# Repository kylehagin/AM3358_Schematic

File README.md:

# AM3358_Schematic
AM3358 Schematic with ram, lcds, and sd card interface.

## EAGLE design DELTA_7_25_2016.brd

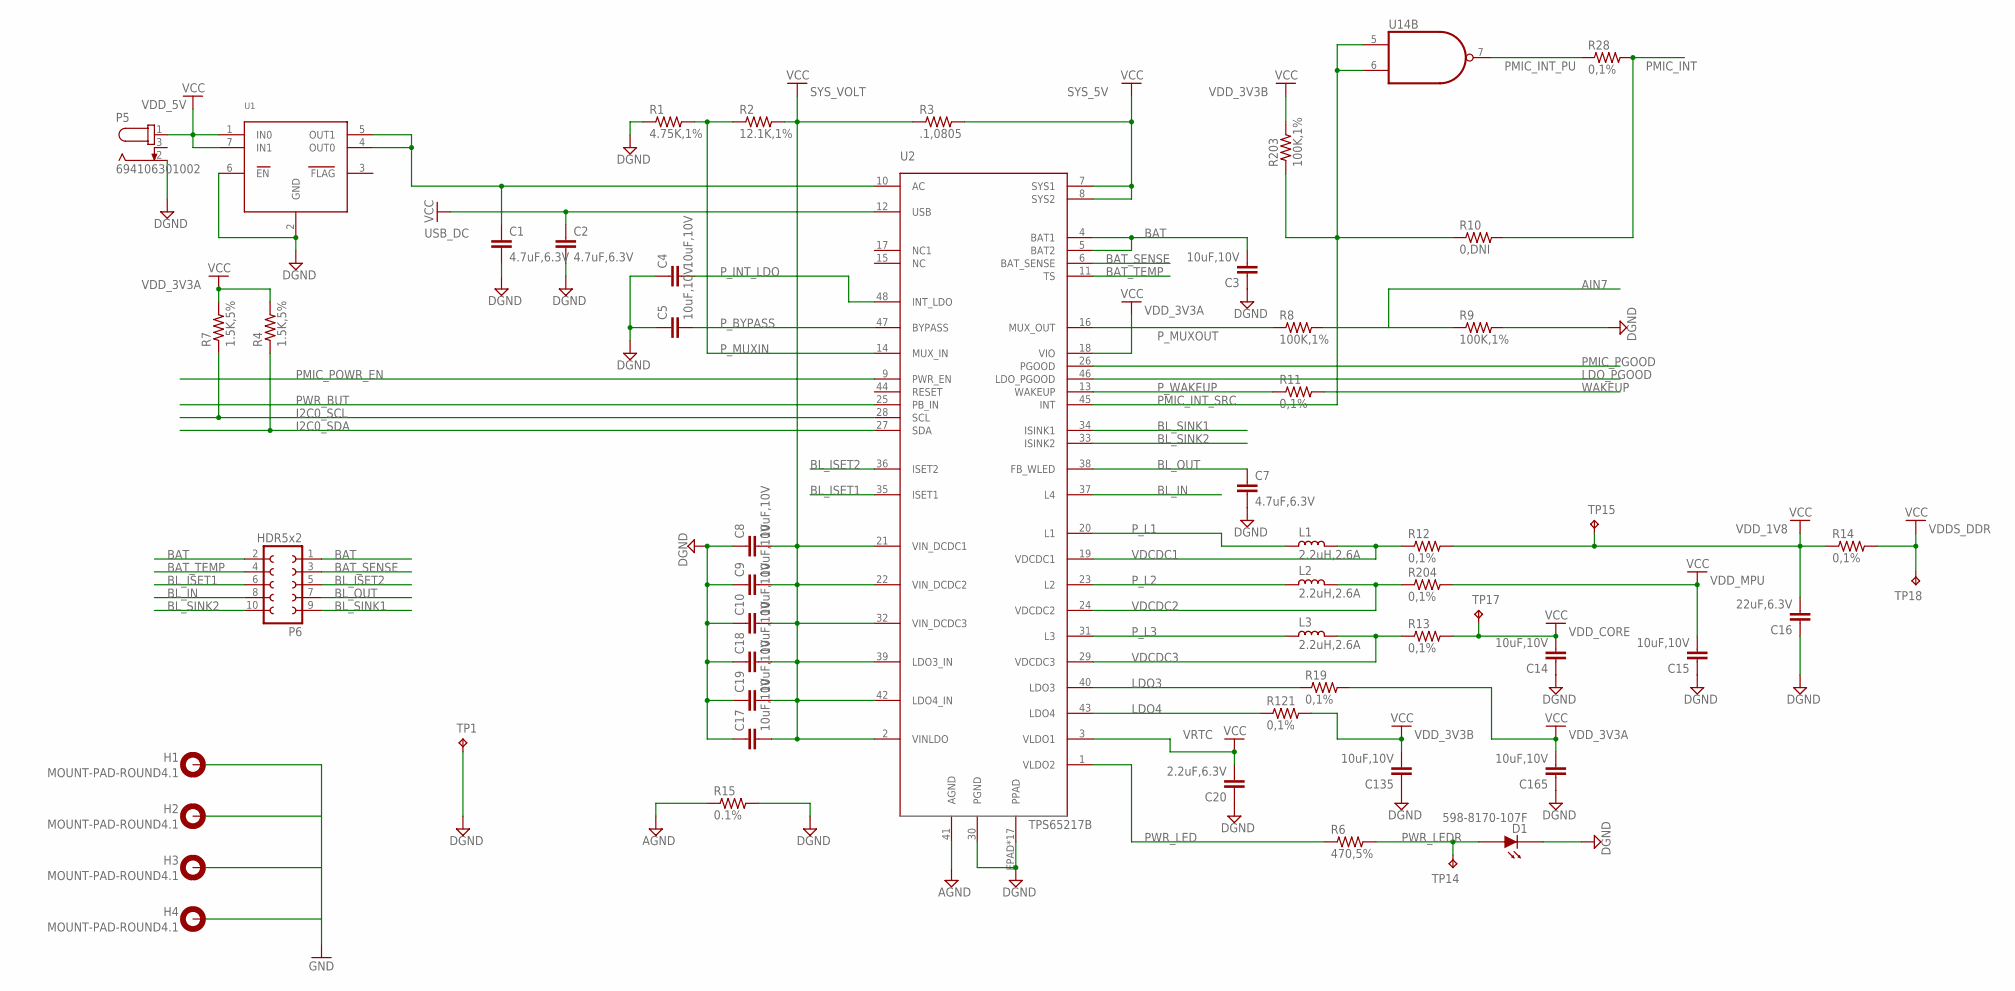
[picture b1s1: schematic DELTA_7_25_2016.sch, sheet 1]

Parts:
C1, C2, C7: 4.7uF,6.3V; C0402
C3, C4, C5, C8, C9, C10, C14, C15, C17, C18, C19, C135, C165: 10uF,10V; C0402
C16: 22uF,6.3V; C0402
C20: 2.2uF,6.3V; C0402
D1: 598-8170-107F; 0805P
H1, H2, H3, H4: MOUNT-PAD-ROUND4.1; 4,1-PAD
L1, L2, L3: 2.2uH,2.6A; L1008
P5: 694106301002
P6: HDR5x2; FE05-2
R1: 4.75K,1%; R0402
R2: 12.1K,1%; R0402
R3: .1,0805; R0402
R4, R7: 1.5K,5%; R0402
R6: 470,5%; R0402
R8, R9, R203: 100K,1%; R0402
R10: 0,DNI; R0402
R11, R12, R13, R14, R19, R28, R121, R204: 0,1%; R0402
R15: 0.1%; R0402
TP1, TP14, TP15, TP17, TP18: TPB1,27; B1,27
U1: NCP349; DFN6
U2: TPS65217B; RSL(S-PVQFN-N48)
U14: SN74LVC2G00DCU; DCU(S-PDSO-G8)

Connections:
AGND: R15.1, U2.41 (AGND)
AIN7: R8.2, R9.1; also elsewhere on the board
BAT: C3.2, P6.1, P6.2, U2.4 (BAT1), U2.5 (BAT2)
BAT_SENSE: P6.3, U2.6 (BAT_SENSE)
BAT_TEMP: P6.4, U2.11 (TS)
BL_IN: P6.8, U2.37 (L4)
BL_ISET1: P6.6, U2.35 (ISET1)
BL_ISET2: P6.5, U2.36 (ISET2)
BL_OUT: C7.1, P6.7, U2.38 (FB_WLED)
BL_SINK1: P6.9, U2.34 (ISINK1)
BL_SINK2: P6.10, U2.33 (ISINK2)
DGND: C1.2, C2.2, C3.1, C4.1, C5.1, C7.2, C8.1, C9.1, C10.1, C14.1, C15.1, C16.1, C17.1, C18.1, C19.1, C20.1, C135.1, C165.1, D1.2 (D_OUT), P5.2, R1.1, R9.2, R15.2, TP1.TP, U1.2 (GND), U1.6 (EN), U2.30 (PGND), U2.EPAD (PPAD), U2.P$1 (PPAD), U2.P$2 (PPAD), U2.P$3 (PPAD), U2.P$4 (PPAD), U2.P$5 (PPAD), U2.P$6 (PPAD), U2.P$7 (PPAD), U2.P$8 (PPAD), U2.P$9 (PPAD), U2.P$10 (PPAD), U2.P$11 (PPAD), U2.P$12 (PPAD), U2.P$13 (PPAD), U2.P$14 (PPAD), U2.P$15 (PPAD), U2.P$16 (PPAD); also elsewhere on the board
GND: H1.B4,1, H2.B4,1, H3.B4,1, H4.B4,1; also elsewhere on the board
I2C0_SCL: R7.1, U2.28 (SCL); also elsewhere on the board
I2C0_SDA: R4.1, U2.27 (SDA); also elsewhere on the board
LDO3: R19.1, U2.40 (LDO3)
LDO4: R121.1, U2.43 (LDO4)
LDO_PGOOD: U2.46 (LDO_PGOOD); also elsewhere on the board
unnamed: C1.1, U1.4 (OUT0), U1.5 (OUT1), U2.10 (AC)
PMIC_INT: R10.2, R28.2; also elsewhere on the board
PMIC_INT_PU: R28.1, U14.7 (O)
PMIC_INT_SRC: R10.1, R203.1, U2.45 (INT), U14.5 (I0), U14.6 (I1)
PMIC_PGOOD: U2.26 (PGOOD); also elsewhere on the board
PMIC_POWR_EN: U2.9 (PWR_EN); also elsewhere on the board
PWR_BUT: U2.25 (PB_IN); also elsewhere on the board
PWR_LED: R6.1, U2.1 (VLDO2)
PWR_LEDR: D1.1 (D_IN), R6.2, TP14.TP
P_BYPASS: C5.2, U2.47 (BYPASS)
P_INT_LDO: C4.2, U2.48 (INT_LDO)
P_L1: L1.2, U2.20 (L1)
P_L2: L2.2, U2.23 (L2)
P_L3: L3.2, U2.31 (L3)
P_MUXIN: R1.2, R2.1, U2.14 (MUX_IN)
P_MUXOUT: R8.1, U2.16 (MUX_OUT)
P_WAKEUP: R11.1, U2.13 (WAKEUP)
SYS_5V: R3.2, U2.7 (SYS1), U2.8 (SYS2); also elsewhere on the board
SYS_VOLT: C8.2, C9.2, C10.2, C17.2, C18.2, C19.2, R2.2, R3.1, U2.2 (VINLDO), U2.21 (VIN_DCDC1), U2.22 (VIN_DCDC2), U2.32 (VIN_DCDC3), U2.39 (LDO3_IN), U2.42 (LDO4_IN); also elsewhere on the board
USB_DC: C2.1, U2.12 (USB); also elsewhere on the board
VDCDC1: L1.1, R12.1, U2.19 (VDCDC1)
VDCDC2: L2.1, R204.1, U2.24 (VDCDC2)
VDCDC3: L3.1, R13.1, U2.29 (VDCDC3)
VDDS_DDR: R14.2, TP18.TP; also elsewhere on the board
VDD_1V8: C16.2, R12.2, R14.1, TP15.TP; also elsewhere on the board
VDD_3V3A: C165.2, R4.2, R7.2, R19.2, U2.18 (VIO); also elsewhere on the board
VDD_3V3B: C135.2, R121.2, R203.2; also elsewhere on the board
VDD_5V: P5.1, U1.1 (IN0), U1.7 (IN1); also elsewhere on the board
VDD_CORE: C14.2, R13.2, TP17.TP; also elsewhere on the board
VDD_MPU: C15.2, R204.2; also elsewhere on the board
VRTC: C20.2, U2.3 (VLDO1); also elsewhere on the board
WAKEUP: R11.2; also elsewhere on the board

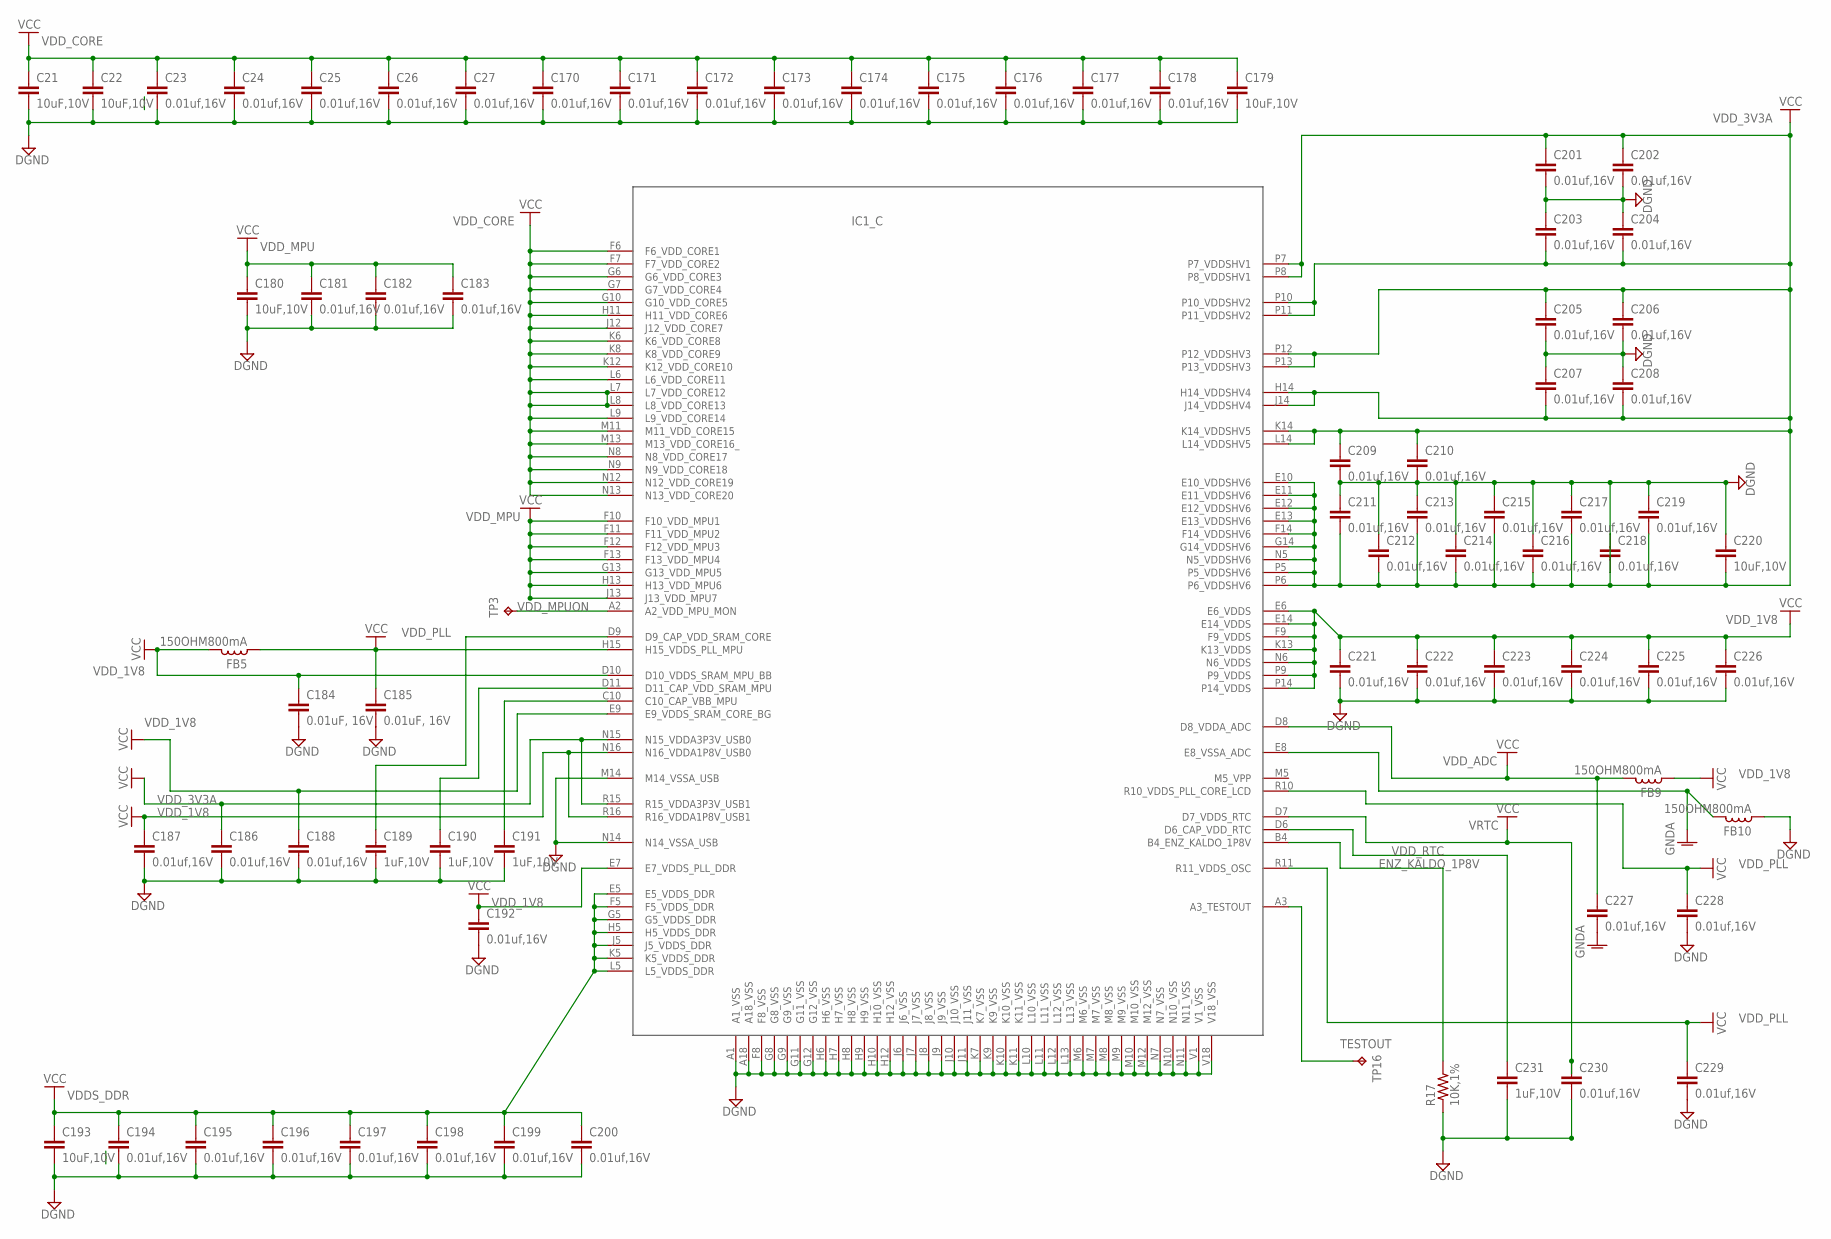
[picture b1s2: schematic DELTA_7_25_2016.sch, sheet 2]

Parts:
C21, C22, C179, C180, C193, C220: 10uF,10V; C0402
C23, C24, C25, C26, C27, C170, C171, C172, C173, C174, C175, C176, C177, C178, C181, C182, C183, C186, C187, C188, C192, C194, C195, C196, C197, C198, C199, C200, C201, C202, C203, C204, C205, C206, C207, C208, C209, C210, C211, C212, C213, C214, C215, C216, C217, C218, C219, C221, C222, C223, C224, C225, C226, C227, C228, C229, C230: 0.01uf,16V; C0402
C184, C185: 0.01uF, 16V; C0402
C189, C190, C191, C231: 1uF,10V; C0402
FB5, FB9: 150OHM800mA; L0603
FB10: 150OHM800mA; L1812
IC1: AM335X_ZCZ; ZCZ_S-PBGA-N324
R17: 10K,1%; R0402
TP3, TP16: TPB1,27; B1,27

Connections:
DGND: C21.2, C22.2, C23.2, C24.2, C25.2, C26.2, C27.2, C170.2, C171.2, C172.2, C173.2, C174.2, C175.2, C176.2, C177.2, C178.2, C179.2, C180.2, C181.2, C182.2, C183.2, C184.2, C185.2, C186.2, C187.2, C188.2, C189.2, C190.2, C191.2, C192.2, C193.2, C194.2, C195.2, C196.2, C197.2, C198.2, C199.2, C200.2, C201.2, C202.2, C203.1, C204.1, C205.2, C206.2, C207.1, C208.1, C221.2, C222.2, C223.2, C224.2, C225.2, C226.2, C228.2, C229.2, C230.2, C231.2, FB10.2, IC1.A1 (A1_VSS), IC1.A18 (A18_VSS), IC1.F8 (F8_VSS), IC1.G8 (G8_VSS), IC1.G9 (G9_VSS), IC1.G11 (G11_VSS), IC1.G12 (G12_VSS), IC1.H6 (H6_VSS), IC1.H7 (H7_VSS), IC1.H8 (H8_VSS), IC1.H9 (H9_VSS), IC1.H10 (H10_VSS), IC1.H12 (H12_VSS), IC1.J6 (J6_VSS), IC1.J7 (J7_VSS), IC1.J8 (J8_VSS), IC1.J9 (J9_VSS), IC1.J10 (J10_VSS), IC1.J11 (J11_VSS), IC1.K7 (K7_VSS), IC1.K9 (K9_VSS), IC1.K10 (K10_VSS), IC1.K11 (K11_VSS), IC1.L10 (L10_VSS), IC1.L11 (L11_VSS), IC1.L12 (L12_VSS), IC1.L13 (L13_VSS), IC1.M6 (M6_VSS), IC1.M7 (M7_VSS), IC1.M8 (M8_VSS), IC1.M9 (M9_VSS), IC1.M10 (M10_VSS), IC1.M12 (M12_VSS), IC1.M14 (M14_VSSA_USB), IC1.N7 (N7_VSS), IC1.N10 (N10_VSS), IC1.N11 (N11_VSS), IC1.N14 (N14_VSSA_USB), IC1.V1 (V1_VSS), IC1.V18 (V18_VSS), R17.1; also elsewhere on the board
ENZ_KALDO_1P8V: IC1.B4 (B4_ENZ_KALDO_1P8V), R17.2
GNDA: C227.2, FB10.1, IC1.E8 (E8_VSSA_ADC); also elsewhere on the board
unnamed: C189.1, IC1.D9 (D9_CAP_VDD_SRAM_CORE)
unnamed: C190.1, IC1.D11 (D11_CAP_VDD_SRAM_MPU)
unnamed: C191.1, IC1.C10 (C10_CAP_VBB_MPU)
TESTOUT: IC1.A3 (A3_TESTOUT), TP16.TP
VDDS_DDR: C193.1, C194.1, C195.1, C196.1, C197.1, C198.1, C199.1, C200.1, IC1.E5 (E5_VDDS_DDR), IC1.F5 (F5_VDDS_DDR), IC1.G5 (G5_VDDS_DDR), IC1.H5 (H5_VDDS_DDR), IC1.J5 (J5_VDDS_DDR), IC1.K5 (K5_VDDS_DDR), IC1.L5 (L5_VDDS_DDR); also elsewhere on the board
VDD_1V8: C184.1, C187.1, C188.1, C192.1, C221.1, C222.1, C223.1, C224.1, C225.1, C226.1, FB5.1, FB9.2, IC1.D10 (D10_VDDS_SRAM_MPU_BB), IC1.E6 (E6_VDDS), IC1.E7 (E7_VDDS_PLL_DDR), IC1.E9 (E9_VDDS_SRAM_CORE_BG), IC1.E14 (E14_VDDS), IC1.F9 (F9_VDDS), IC1.K13 (K13_VDDS), IC1.N6 (N6_VDDS), IC1.N16 (N16_VDDA1P8V_USB0), IC1.P9 (P9_VDDS), IC1.P14 (P14_VDDS), IC1.R16 (R16_VDDA1P8V_USB1); also elsewhere on the board
VDD_3V3A: C186.1, C201.1, C202.1, C203.2, C204.2, C205.1, C206.1, C207.2, C208.2, C209.1, C209.2, C210.1, C210.2, C211.1, C211.2, C212.1, C212.2, C213.1, C213.2, C214.1, C214.2, C215.1, C215.2, C216.1, C216.2, C217.1, C217.2, C218.1, C218.2, C219.1, C219.2, C220.1, C220.2, IC1.E10 (E10_VDDSHV6), IC1.E11 (E11_VDDSHV6), IC1.E12 (E12_VDDSHV6), IC1.E13 (E13_VDDSHV6), IC1.F14 (F14_VDDSHV6), IC1.G14 (G14_VDDSHV6), IC1.H14 (H14_VDDSHV4), IC1.J14 (J14_VDDSHV4), IC1.K14 (K14_VDDSHV5), IC1.L14 (L14_VDDSHV5), IC1.N5 (N5_VDDSHV6), IC1.N15 (N15_VDDA3P3V_USB0), IC1.P5 (P5_VDDSHV6), IC1.P6 (P6_VDDSHV6), IC1.P7 (P7_VDDSHV1), IC1.P8 (P8_VDDSHV1), IC1.P10 (P10_VDDSHV2), IC1.P11 (P11_VDDSHV2), IC1.P12 (P12_VDDSHV3), IC1.P13 (P13_VDDSHV3), IC1.R15 (R15_VDDA3P3V_USB1); also elsewhere on the board
VDD_ADC: C227.1, FB9.1, IC1.D8 (D8_VDDA_ADC); also elsewhere on the board
VDD_CORE: C21.1, C22.1, C23.1, C24.1, C25.1, C26.1, C27.1, C170.1, C171.1, C172.1, C173.1, C174.1, C175.1, C176.1, C177.1, C178.1, C179.1, IC1.F6 (F6_VDD_CORE1), IC1.F7 (F7_VDD_CORE2), IC1.G6 (G6_VDD_CORE3), IC1.G7 (G7_VDD_CORE4), IC1.G10 (G10_VDD_CORE5), IC1.H11 (H11_VDD_CORE6), IC1.J12 (J12_VDD_CORE7), IC1.K6 (K6_VDD_CORE8), IC1.K8 (K8_VDD_CORE9), IC1.K12 (K12_VDD_CORE10), IC1.L6 (L6_VDD_CORE11), IC1.L7 (L7_VDD_CORE12), IC1.L8 (L8_VDD_CORE13), IC1.L9 (L9_VDD_CORE14), IC1.M11 (M11_VDD_CORE15), IC1.M13 (M13_VDD_CORE16_), IC1.N8 (N8_VDD_CORE17), IC1.N9 (N9_VDD_CORE18), IC1.N12 (N12_VDD_CORE19), IC1.N13 (N13_VDD_CORE20); also elsewhere on the board
VDD_MPU: C180.1, C181.1, C182.1, C183.1, IC1.F10 (F10_VDD_MPU1), IC1.F11 (F11_VDD_MPU2), IC1.F12 (F12_VDD_MPU3), IC1.F13 (F13_VDD_MPU4), IC1.G13 (G13_VDD_MPU5), IC1.H13 (H13_VDD_MPU6), IC1.J13 (J13_VDD_MPU7); also elsewhere on the board
VDD_MPUON: IC1.A2 (A2_VDD_MPU_MON), TP3.TP
VDD_PLL: C185.1, C228.1, C229.1, FB5.2, IC1.H15 (H15_VDDS_PLL_MPU), IC1.R10 (R10_VDDS_PLL_CORE_LCD), IC1.R11 (R11_VDDS_OSC)
VDD_RTC: C231.1, IC1.D6 (D6_CAP_VDD_RTC)
VRTC: C230.1, IC1.D7 (D7_VDDS_RTC); also elsewhere on the board

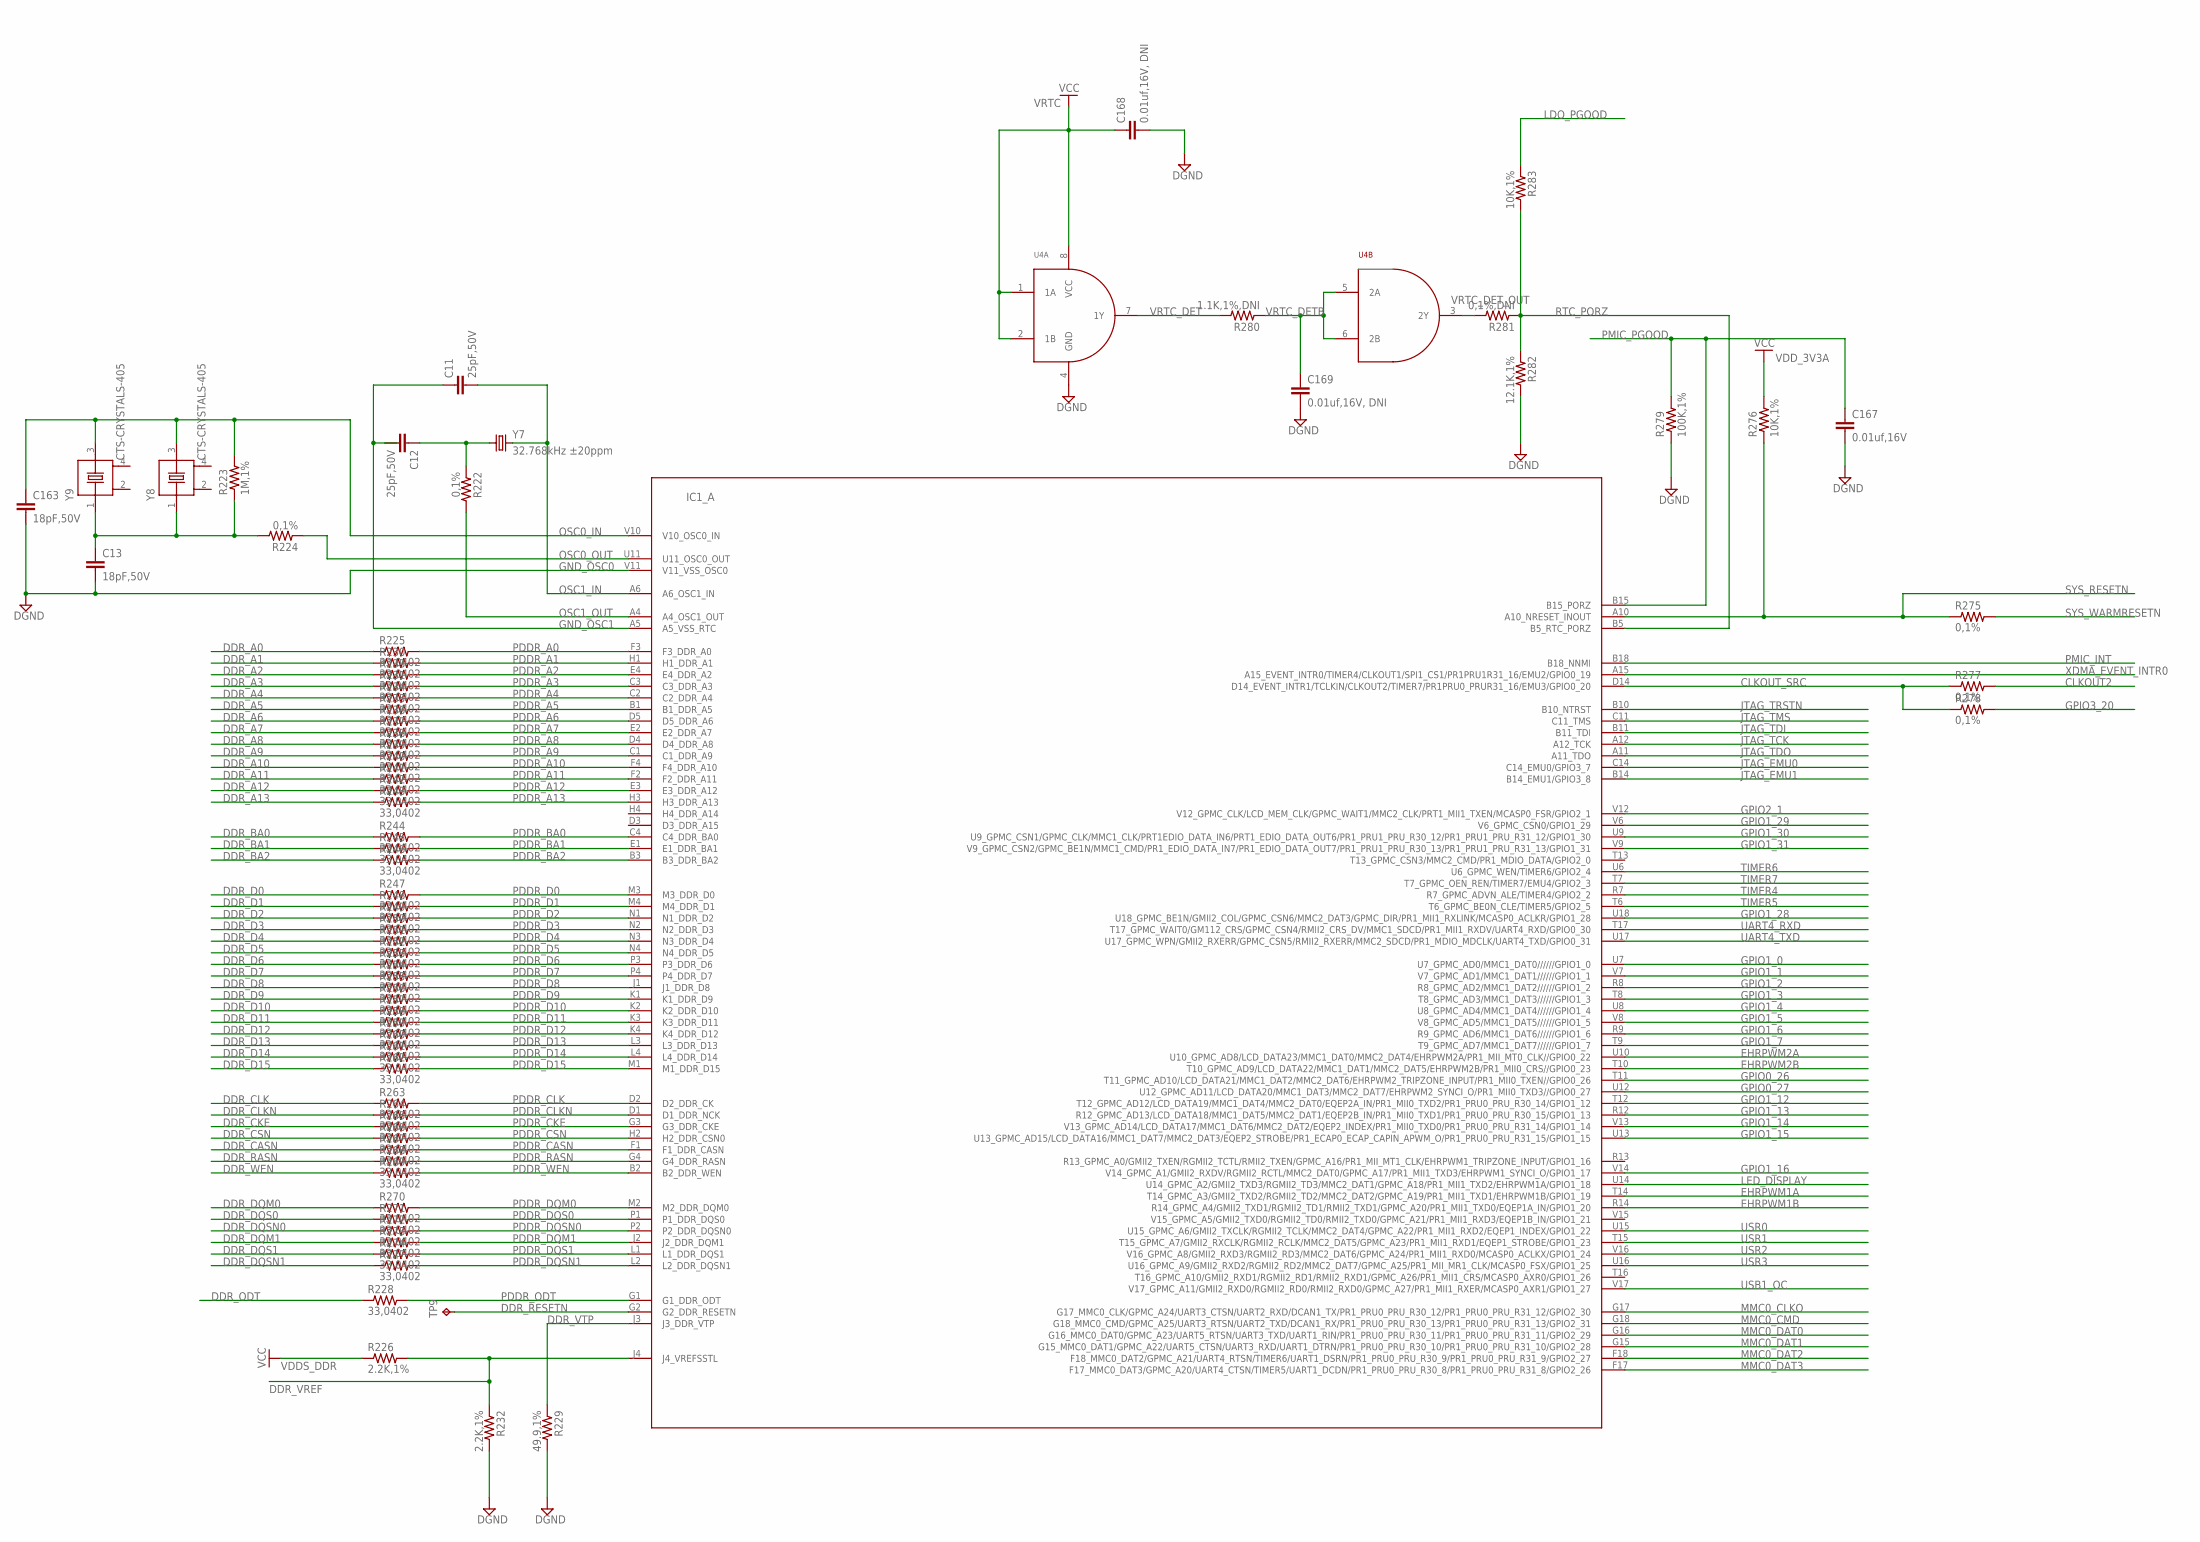
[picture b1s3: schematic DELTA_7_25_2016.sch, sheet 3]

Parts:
C11, C12: 25pF,50V; C0603
C13, C163: 18pF,50V; C0402
C167: 0.01uf,16V; C0402
C168, C169: 0.01uf,16V, DNI; C0402
IC1: AM335X_ZCZ; ZCZ_S-PBGA-N324
R222, R224, R275, R277, R278: 0,1%; R0402
R223: 1M,1%; R0402
R225, R227, R228, R230, R231, R233, R234, R235, R236, R237, R238, R239, R240, R241, R242, R243, R244, R245, R246, R247, R248, R249, R250, R251, R252, R253, R254, R255, R256, R257, R258, R259, R260, R261, R262, R263, R264, R265, R266, R267, R268, R269, R270, R271, R272, R273, R274: 33,0402; R0402
R226, R232: 2.2K,1%; R0402
R229: 49.9,1%; R0402
R276, R283: 10K,1%; R0402
R279: 100K,1%; R0402
R280: 1.1K,1%,DNI; R0402
R281: 0,1%,DNI; R0402
R282: 12.1K,1%; R0402
TP9: TPB1,27; B1,27
U4: SN74AUP2G08,DNI; DQE(R-PX2SON-N8),DNI
Y7: 32.768kHz ±20ppm; MC-306
Y8, Y9: CTS-CRYSTALS-405; CTS-405

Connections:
CLKOUT2: R277.2; also elsewhere on the board
CLKOUT_SRC: IC1.D14 (D14_EVENT_INTR1/TCLKIN/CLKOUT2/TIMER7/P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), R277.1, R278.1
DDR_A0: R225.1; also elsewhere on the board
DDR_A1: R230.1; also elsewhere on the board
DDR_A2: R233.1; also elsewhere on the board
DDR_A3: R231.1; also elsewhere on the board
DDR_A4: R234.1; also elsewhere on the board
DDR_A5: R235.1; also elsewhere on the board
DDR_A6: R236.1; also elsewhere on the board
DDR_A7: R237.1; also elsewhere on the board
DDR_A8: R238.1; also elsewhere on the board
DDR_A9: R239.1; also elsewhere on the board
DDR_A10: R240.1; also elsewhere on the board
DDR_A11: R241.1; also elsewhere on the board
DDR_A12: R242.1; also elsewhere on the board
DDR_A13: R243.1; also elsewhere on the board
DDR_BA0: R244.1; also elsewhere on the board
DDR_BA1: R245.1; also elsewhere on the board
DDR_BA2: R246.1; also elsewhere on the board
DDR_CASN: R267.1; also elsewhere on the board
DDR_CKE: R265.1; also elsewhere on the board
DDR_CLK: R263.1; also elsewhere on the board
DDR_CLKN: R264.1; also elsewhere on the board
DDR_CSN: R266.1; also elsewhere on the board
DDR_D0: R247.1; also elsewhere on the board
DDR_D1: R248.1; also elsewhere on the board
DDR_D2: R249.1; also elsewhere on the board
DDR_D3: R250.1; also elsewhere on the board
DDR_D4: R251.1; also elsewhere on the board
DDR_D5: R252.1; also elsewhere on the board
DDR_D6: R253.1; also elsewhere on the board
DDR_D7: R254.1; also elsewhere on the board
DDR_D8: R255.1; also elsewhere on the board
DDR_D9: R256.1; also elsewhere on the board
DDR_D10: R257.1; also elsewhere on the board
DDR_D11: R258.1; also elsewhere on the board
DDR_D12: R259.1; also elsewhere on the board
DDR_D13: R260.1; also elsewhere on the board
DDR_D14: R261.1; also elsewhere on the board
DDR_D15: R262.1; also elsewhere on the board
DDR_DQM0: R270.1; also elsewhere on the board
DDR_DQM1: R273.1; also elsewhere on the board
DDR_DQS0: R271.1; also elsewhere on the board
DDR_DQS1: R274.1; also elsewhere on the board
DDR_DQSN0: R272.1; also elsewhere on the board
DDR_DQSN1: R227.1; also elsewhere on the board
DDR_ODT: R228.1; also elsewhere on the board
DDR_RASN: R268.1; also elsewhere on the board
DDR_RESETN: IC1.G2 (G2_DDR_RESETN), TP9.TP; also elsewhere on the board
DDR_VREF: IC1.J4 (J4_VREFSSTL), R226.2, R232.1; also elsewhere on the board
DDR_VTP: IC1.J3 (J3_DDR_VTP), R229.1
DDR_WEN: R269.1; also elsewhere on the board
DGND: C167.2, C168.2, C169.2, R229.2, R232.2, R279.1, R282.2, U4.4 (GND); also elsewhere on the board
EHRPWM1A: IC1.T14 (T14_GPMC_A3/GMII2_TXD2/RGMII2_TD2/MMC2_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); also elsewhere on the board
EHRPWM1B: IC1.R14 (R14_GPMC_A4/GMII2_TXD1/RGMII2_TD1/RMII2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); also elsewhere on the board
EHRPWM2A: IC1.U10 (U10_GPMC_AD8/LCD_DATA23/MMC1_DAT0/MMC2_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); also elsewhere on the board
EHRPWM2B: IC1.T10 (T10_GPMC_AD9/LCD_DATA22/MMC1_DAT1/MMC2_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); also elsewhere on the board
GND_OSC0: C13.2, C163.2, IC1.V11 (V11_VSS_OSC0)
GND_OSC1: C11.1, C12.2, IC1.A5 (A5_VSS_RTC)
GPIO0_26: IC1.T11 (T11_GPMC_AD10/LCD_DATA21/MMC1_DAT2/MMC2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); also elsewhere on the board
GPIO0_27: IC1.U12 (U12_GPMC_AD11/LCD_DATA20/MMC1_DAT3/MMC2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); also elsewhere on the board
GPIO1_0: IC1.U7 (U7_GPMC_AD0/MMC1_DAT0//////GPIO1_0); also elsewhere on the board
GPIO1_1: IC1.V7 (V7_GPMC_AD1/MMC1_DAT1//////GPIO1_1)
GPIO1_2: IC1.R8 (R8_GPMC_AD2/MMC1_DAT2//////GPIO1_2); also elsewhere on the board
GPIO1_3: IC1.T8 (T8_GPMC_AD3/MMC1_DAT3//////GPIO1_3); also elsewhere on the board
GPIO1_4: IC1.U8 (U8_GPMC_AD4/MMC1_DAT4//////GPIO1_4); also elsewhere on the board
GPIO1_5: IC1.V8 (V8_GPMC_AD5/MMC1_DAT5//////GPIO1_5); also elsewhere on the board
GPIO1_6: IC1.R9 (R9_GPMC_AD6/MMC1_DAT6//////GPIO1_6); also elsewhere on the board
GPIO1_7: IC1.T9 (T9_GPMC_AD7/MMC1_DAT7//////GPIO1_7); also elsewhere on the board
GPIO1_12: IC1.T12 (T12_GPMC_AD12/LCD_DATA19/MMC1_DAT4/MMC2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); also elsewhere on the board
GPIO1_13: IC1.R12 (R12_GPMC_AD13/LCD_DATA18/MMC1_DAT5/MMC2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); also elsewhere on the board
GPIO1_14: IC1.V13 (V13_GPMC_AD14/LCD_DATA17/MMC1_DAT6/MMC2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); also elsewhere on the board
GPIO1_15: IC1.U13 (U13_GPMC_AD15/LCD_DATA16/MMC1_DAT7/MMC2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); also elsewhere on the board
GPIO1_16: IC1.V14 (V14_GPMC_A1/GMII2_RXDV/RGMII2_RCTL/MMC2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); also elsewhere on the board
GPIO1_28: IC1.U18 (U18_GPMC_BE1N/GMII2_COL/GPMC_CSN6/MMC2_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); also elsewhere on the board
GPIO1_29: IC1.V6 (V6_GPMC_CSN0/GPIO1_29); also elsewhere on the board
GPIO1_30: IC1.U9 (U9_GPMC_CSN1/GPMC_CLK/MMC1_CLK/PRT1EDIO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); also elsewhere on the board
GPIO1_31: IC1.V9 (V9_GPMC_CSN2/GPMC_BE1N/MMC1_CMD/PR1_EDI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); also elsewhere on the board
GPIO2_1: IC1.V12 (V12_GPMC_CLK/LCD_MEM_CLK/GPMC_WAIT1/MMC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); also elsewhere on the board
GPIO3_20: R278.2; also elsewhere on the board
JTAG_EMU0: IC1.C14 (C14_EMU0/GPIO3_7); also elsewhere on the board
JTAG_EMU1: IC1.B14 (B14_EMU1/GPIO3_8); also elsewhere on the board
JTAG_TCK: IC1.A12 (A12_TCK); also elsewhere on the board
JTAG_TDI: IC1.B11 (B11_TDI); also elsewhere on the board
JTAG_TDO: IC1.A11 (A11_TDO); also elsewhere on the board
JTAG_TMS: IC1.C11 (C11_TMS); also elsewhere on the board
JTAG_TRSTN: IC1.B10 (B10_NTRST); also elsewhere on the board
LDO_PGOOD: R283.1; also elsewhere on the board
LED_DISPLAY: IC1.U14 (U14_GPMC_A2/GMII2_TXD3/RGMII2_TD3/MMC2_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); also elsewhere on the board
MMC0_CLKO: IC1.G17 (G17_MMC0_CLK/GPMC_A24/UART3_CTSN/UART2_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); also elsewhere on the board
MMC0_CMD: IC1.G18 (G18_MMC0_CMD/GPMC_A25/UART3_RTSN/UART2_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); also elsewhere on the board
MMC0_DAT0: IC1.G16 (G16_MMC0_DAT0/GPMC_A23/UART5_RTSN/UART3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); also elsewhere on the board
MMC0_DAT1: IC1.G15 (G15_MMC0_DAT1/GPMC_A22/UART5_CTSN/UART3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); also elsewhere on the board
MMC0_DAT2: IC1.F18 (F18_MMC0_DAT2/GPMC_A21/UART4_RTSN/TIMER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); also elsewhere on the board
MMC0_DAT3: IC1.F17 (F17_MMC0_DAT3/GPMC_A20/UART4_CTSN/TIMER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); also elsewhere on the board
unnamed: C12.1, R222.1, Y7.1
unnamed: C13.1, R223.1, R224.2, Y8.1, Y9.1
OSC0_IN: C163.1, IC1.V10 (V10_OSC0_IN), R223.2, Y8.3, Y9.3
OSC0_OUT: IC1.U11 (U11_OSC0_OUT), R224.1
OSC1_IN: C11.2, IC1.A6 (A6_OSC1_IN), Y7.4 (2)
OSC1_OUT: IC1.A4 (A4_OSC1_OUT), R222.2
PDDR_A0: IC1.F3 (F3_DDR_A0), R225.2
PDDR_A1: IC1.H1 (H1_DDR_A1), R230.2
PDDR_A2: IC1.E4 (E4_DDR_A2), R233.2
PDDR_A3: IC1.C3 (C3_DDR_A3), R231.2
PDDR_A4: IC1.C2 (C2_DDR_A4), R234.2
PDDR_A5: IC1.B1 (B1_DDR_A5), R235.2
PDDR_A6: IC1.D5 (D5_DDR_A6), R236.2
PDDR_A7: IC1.E2 (E2_DDR_A7), R237.2
PDDR_A8: IC1.D4 (D4_DDR_A8), R238.2
PDDR_A9: IC1.C1 (C1_DDR_A9), R239.2
PDDR_A10: IC1.F4 (F4_DDR_A10), R240.2
PDDR_A11: IC1.F2 (F2_DDR_A11), R241.2
PDDR_A12: IC1.E3 (E3_DDR_A12), R242.2
PDDR_A13: IC1.H3 (H3_DDR_A13), R243.2
PDDR_BA0: IC1.C4 (C4_DDR_BA0), R244.2
PDDR_BA1: IC1.E1 (E1_DDR_BA1), R245.2
PDDR_BA2: IC1.B3 (B3_DDR_BA2), R246.2
PDDR_CASN: IC1.F1 (F1_DDR_CASN), R267.2
PDDR_CKE: IC1.G3 (G3_DDR_CKE), R265.2
PDDR_CLK: IC1.D2 (D2_DDR_CK), R263.2
PDDR_CLKN: IC1.D1 (D1_DDR_NCK), R264.2
PDDR_CSN: IC1.H2 (H2_DDR_CSN0), R266.2
PDDR_D0: IC1.M3 (M3_DDR_D0), R247.2
PDDR_D1: IC1.M4 (M4_DDR_D1), R248.2
PDDR_D2: IC1.N1 (N1_DDR_D2), R249.2
PDDR_D3: IC1.N2 (N2_DDR_D3), R250.2
PDDR_D4: IC1.N3 (N3_DDR_D4), R251.2
PDDR_D5: IC1.N4 (N4_DDR_D5), R252.2
PDDR_D6: IC1.P3 (P3_DDR_D6), R253.2
PDDR_D7: IC1.P4 (P4_DDR_D7), R254.2
PDDR_D8: IC1.J1 (J1_DDR_D8), R255.2
PDDR_D9: IC1.K1 (K1_DDR_D9), R256.2
PDDR_D10: IC1.K2 (K2_DDR_D10), R257.2
PDDR_D11: IC1.K3 (K3_DDR_D11), R258.2
PDDR_D12: IC1.K4 (K4_DDR_D12), R259.2
PDDR_D13: IC1.L3 (L3_DDR_D13), R260.2
PDDR_D14: IC1.L4 (L4_DDR_D14), R261.2
PDDR_D15: IC1.M1 (M1_DDR_D15), R262.2
PDDR_DQM0: IC1.M2 (M2_DDR_DQM0), R270.2
PDDR_DQM1: IC1.J2 (J2_DDR_DQM1), R273.2
PDDR_DQS0: IC1.P1 (P1_DDR_DQS0), R271.2
PDDR_DQS1: IC1.L1 (L1_DDR_DQS1), R274.2
PDDR_DQSN0: IC1.P2 (P2_DDR_DQSN0), R272.2
PDDR_DQSN1: IC1.L2 (L2_DDR_DQSN1), R227.2
PDDR_ODT: IC1.G1 (G1_DDR_ODT), R228.2
PDDR_RASN: IC1.G4 (G4_DDR_RASN), R268.2
PDDR_WEN: IC1.B2 (B2_DDR_WEN), R269.2
PMIC_INT: IC1.B18 (B18_NNMI); also elsewhere on the board
PMIC_PGOOD: C167.1, IC1.B15 (B15_PORZ), R279.2; also elsewhere on the board
RTC_PORZ: IC1.B5 (B5_RTC_PORZ), R281.1, R282.1, R283.2
SYS_RESETN: IC1.A10 (A10_NRESET_INOUT), R275.1, R276.1; also elsewhere on the board
SYS_WARMRESETN: R275.2; also elsewhere on the board
TIMER4: IC1.R7 (R7_GPMC_ADVN_ALE/TIMER4/GPIO2_2); also elsewhere on the board
TIMER5: IC1.T6 (T6_GPMC_BE0N_CLE/TIMER5/GPIO2_5); also elsewhere on the board
TIMER6: IC1.U6 (U6_GPMC_WEN/TIMER6/GPIO2_4); also elsewhere on the board
TIMER7: IC1.T7 (T7_GPMC_OEN_REN/TIMER7/EMU4/GPIO2_3); also elsewhere on the board
UART4_RXD: IC1.T17 (T17_GPMC_WAIT0/GM112_CRS/GPMC_CSN4/RMII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); also elsewhere on the board
UART4_TXD: IC1.U17 (U17_GPMC_WPN/GMII2_RXERR/GPMC_CSN5/RMII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); also elsewhere on the board
USB1_OC: IC1.V17 (V17_GPMC_A11/GMII2_RXD0/RGMII2_RD0/RMII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); also elsewhere on the board
USR0: IC1.U15 (U15_GPMC_A6/GMII2_TXCLK/RGMII2_TCLK/MMC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); also elsewhere on the board
USR1: IC1.T15 (T15_GPMC_A7/GMII2_RXCLK/RGMII2_RCLK/MMC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); also elsewhere on the board
USR2: IC1.V16 (V16_GPMC_A8/GMII2_RXD3/RGMII2_RD3/MMC2_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); also elsewhere on the board
USR3: IC1.U16 (U16_GPMC_A9/GMII2_RXD2/RGMII2_RD2/MMC2_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); also elsewhere on the board
VDDS_DDR: R226.1; also elsewhere on the board
VDD_3V3A: R276.2; also elsewhere on the board
VRTC: C168.1, U4.1 (1A), U4.2 (1B), U4.8 (VCC); also elsewhere on the board
VRTC_DET: R280.2, U4.7 (1Y)
VRTC_DETB: C169.1, R280.1, U4.5 (2A), U4.6 (2B)
VRTC_DET_OUT: R281.2, U4.3 (2Y)
XDMA_EVENT_INTR0: IC1.A15 (A15_EVENT_INTR0/TIMER4/CLKOUT1/SPI1_CS1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); also elsewhere on the board

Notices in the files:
parts and their libraries:
Wurth_Elektronik_Passive_rev15d: Copyright: Würth Elektronik
con-fci: Copyright (C) 2008, Bob Starr
